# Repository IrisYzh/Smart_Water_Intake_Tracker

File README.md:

# Smart Water Intake Tracker

*The Smart Water Intake Tracker is a physical, non-intrusive system that helps users track their daily water intake through passive sensing and dynamic feedback.*  

This project consists of a smart sensing coaster and a desktop display device that together track and visualize a user’s daily water intake.

By passively detecting drinking events through weight changes and presenting progress via a mechanical gauge, the system encourages hydration without relying on screens or manual input.

---

## Sensor Device: Smart Coaster

### How it works
The sensing device is a smart coaster placed under a cup or bottle that detects drinking activity by monitoring weight changes. 

A load cell measures the applied force, and the signal is amplified, digitized, and processed by a microcontroller to estimate water intake based on relative weight differences over time.

### Key features
- **Drink Detection**: When the sensor detects that the cup has been lifted, the LED on the coaster begins to pulse, indicating that it's monitoring for weight changes.

- **Upload Status**: Once the weight change is detected and successfully uploaded to the display device, the coaster lights up green for 3 seconds. If the upload fails, it lights up red for 3 seconds instead.

- **Hydration Reminder**: If the system detects that the user hasn't had any water for 2 hours (no weight changes detected), the coaster will pulse to remind the user to stay hydrated.

### Key components
- **RGB LED**: [NeoPixel](Datasheets/SK6812RGBW-Neopixel.pdf)
- [**TAL221 Load Cell**](Datasheets/TAL221.pdf)  
- [**HX711 Load Cell Amplifier**](Datasheets/hx711_english.pdf)
- [**Seeed Studio XIAO ESP32-C3**](Datasheets/Seeed-Studio-XIAO-Series-SOM-Datasheet.pdf)
- **Communication**: Bluetooth Low Energy (BLE)

### Usage Modes
- **Sleep**: Device is off, minimal power consumption

- **Monitoring**: Continuously checks weight every 3 seconds with LED feedback

- **Detecting**: Actively detects weight changes and transmits data via BLE

---

## Display Device: Desktop Hydration Gauge

### How it works
The display device is a desktop hydration gauge that gives you a quick view of your daily water intake. It has a mechanical needle that shows your progress from 0–100%, an RGB LED ring for color-coded feedback, and a physical reset button to restart daily tracking.

### Key features
- **Visual Progress Tracking**: When the gauge receives a signal from the coaster, the needle moves to show how much water you've drunk today. The OLED screen below displays the exact amount and your progress percentage toward the daily goal.

- **Customizable Goals**: You can press the button below the dial to reset your data, or use the rotary knob to adjust your target water intake. All information shows up on the OLED screen.

### Key components
- **X27 Stepper Motor**
- **RGB LED**: [NeoPixel](Datasheets/SK6812RGBW-Neopixel.pdf)
- [**Seeed Studio XIAO ESP32-C3**](Datasheets/Seeed-Studio-XIAO-Series-SOM-Datasheet.pdf)
- [**SSD1306 OLED**](Datasheets/SSD1306.pdf) (Show the number)
- [**Rotary encoder**](Datasheets/RotaryEncoder-pec11.pdf) (Set/Change the goal)
- **Reset button**
- **Communication**: Bluetooth Low Energy (BLE)

### Usage Modes
- **Sleep**: Device is off, screen and motors powered down

- **Displaying**: Shows current hydration data with ambient lighting

- **Adjusting**: User interacts with buttons and rotary encoder to change settings

---

## Device-to-device communication

The smart coaster sends processed intake data to the display device wirelessly using Bluetooth Low Energy (BLE).  
Only high-level intake events (e.g., estimated water consumed) are transmitted, minimizing bandwidth and power usage.

### System workflow
1. The load cell detects weight changes when the user interacts with the cup  
2. The HX711 amplifies and digitizes the signal  
3. The microcontroller filters noise and detects valid drinking events  
4. Estimated intake values are accumulated locally  
5. Intake data is transmitted via BLE to the display device  
6. The display updates the mechanical needle and LED ring in real time  

This modular architecture separates sensing and feedback, making the system easier to debug, extend, and maintain.

## System Architecture

### Schematic

### PCB Design

---

## Datasheets

All component datasheets are included in the `/datasheets` folder of this repository.

- [TAL221 Load Cell Datasheet](Datasheets/TAL221.pdf)  
- [HX711 Load Cell Amplifier](Datasheets/hx711_english.pdf)  
- [Seeed Studio XIAO ESP32-C3](Datasheets/Seeed-Studio-XIAO-Series-SOM-Datasheet.pdf)  
- [OLED SSD1306](Datasheets/SSD1306.pdf)
- [Rotary Encoder](Datasheets/RotaryEncoder-pec11.pdf)
- [Neopixel](Datasheets/SK6812RGBW-Neopixel.pdf)

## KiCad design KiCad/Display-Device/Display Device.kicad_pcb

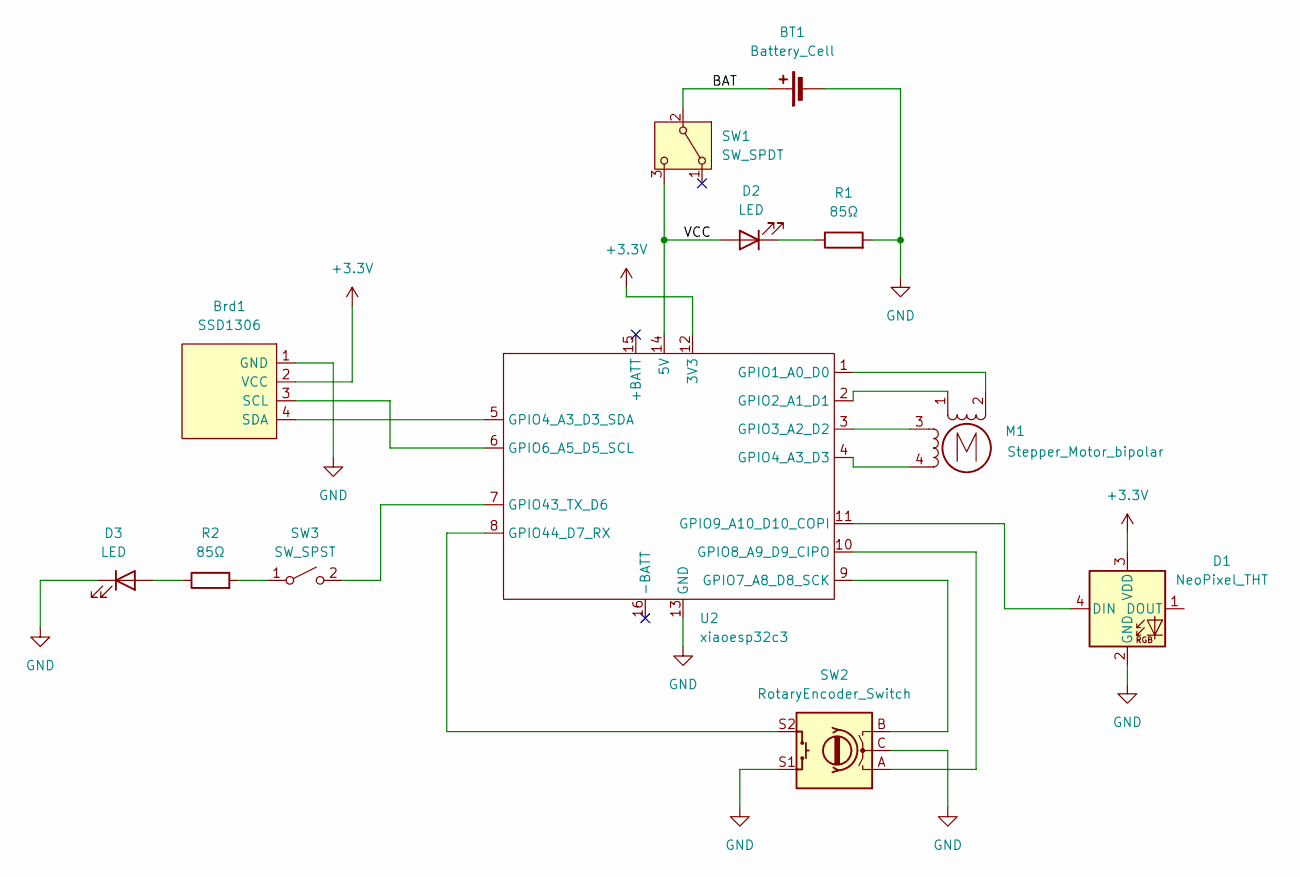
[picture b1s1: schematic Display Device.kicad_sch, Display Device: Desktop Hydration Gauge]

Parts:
BT1: Battery_Cell; PinSocket_1x02_P2.54mm_Vertical
Brd1: SSD1306; 128x64OLED
D1: NeoPixel_THT; PinSocket_1x04_P2.54mm_Vertical
D2, D3: LED; LED_0805_2012Metric_Pad1.15x1.40mm_HandSolder
M1: Stepper_Motor_bipolar; x27_stepper
R1, R2: 85Ω; R_0805_2012Metric_Pad1.20x1.40mm_HandSolder
SW1: SW_SPDT; PinSocket_1x03_P2.54mm_Vertical
SW2: RotaryEncoder_Switch; RotaryEncoder_Alps_EC11E-Switch_Vertical_H20mm
SW3: SW_SPST; PinSocket_1x02_P2.54mm_Vertical
U2: xiaoesp32c3; XIAO_ESP32

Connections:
+3.3V: Brd1.2 (VCC), D1.3 (VDD), U2.12 (3V3)
/BAT: BT1.1 (+), SW1.2 (B)
/VCC: D2.2 (A), SW1.3 (C), U2.14 (5V)
GND: BT1.2 (-), Brd1.1 (GND), D1.2 (GND), D3.1 (K), R1.2, SW2.C, SW2.S1, U2.13 (GND)
unnamed: Brd1.3 (SCL), U2.6 (GPIO6_A5_D5_SCL)
unnamed: Brd1.4 (SDA), U2.5 (GPIO4_A3_D3_SDA)
unnamed: D1.4 (DIN), U2.11 (GPIO9_A10_D10_COPI)
unnamed: D2.1 (K), R1.1
unnamed: D3.2 (A), R2.1
unnamed: M1.2 (-), U2.1 (GPIO1_A0_D0)
unnamed: R2.2, SW3.1 (A)
unnamed: SW3.2 (B), U2.7 (GPIO43_TX_D6)
unnamed: M1.1, U2.2 (GPIO2_A1_D1)
unnamed: M1.3, U2.3 (GPIO3_A2_D2)
unnamed: M1.4, U2.4 (GPIO4_A3_D3)
unnamed: SW2.B, U2.9 (GPIO7_A8_D8_SCK)
unnamed: SW2.A, U2.10 (GPIO8_A9_D9_CIPO)
unnamed: SW2.S2, U2.8 (GPIO44_D7_RX)

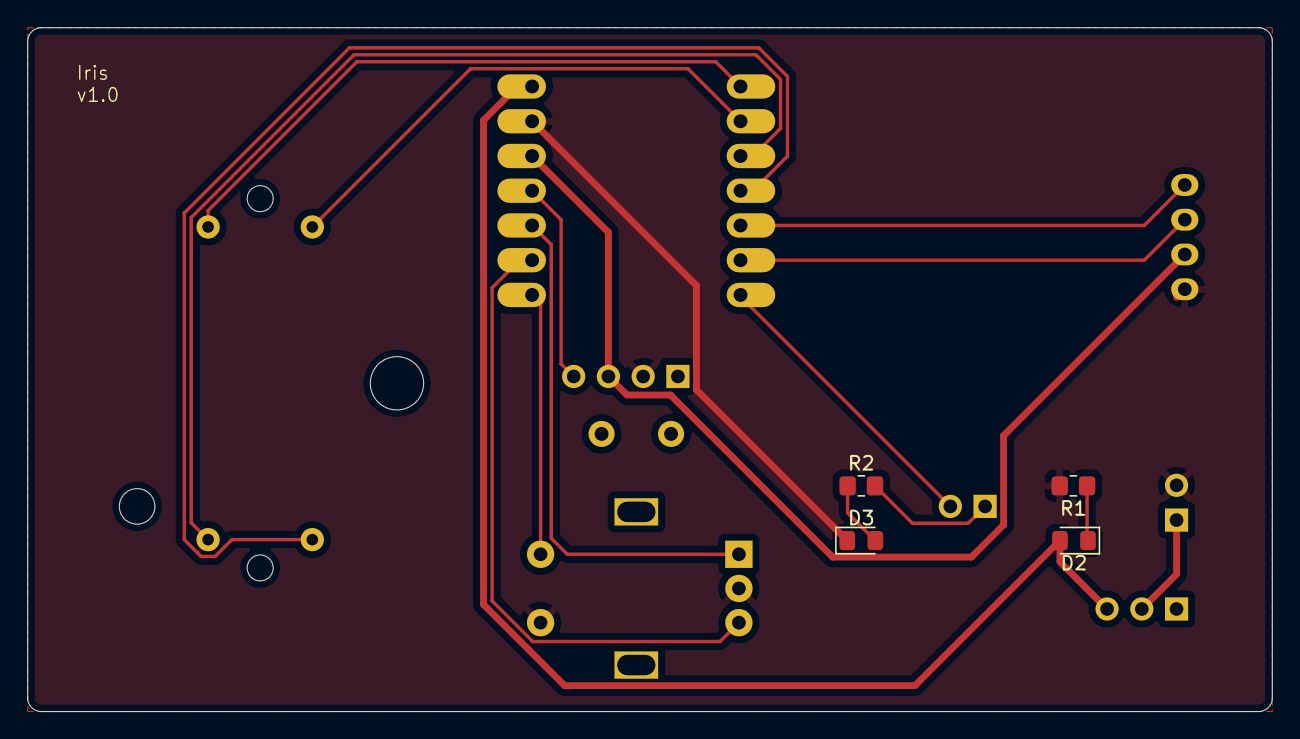
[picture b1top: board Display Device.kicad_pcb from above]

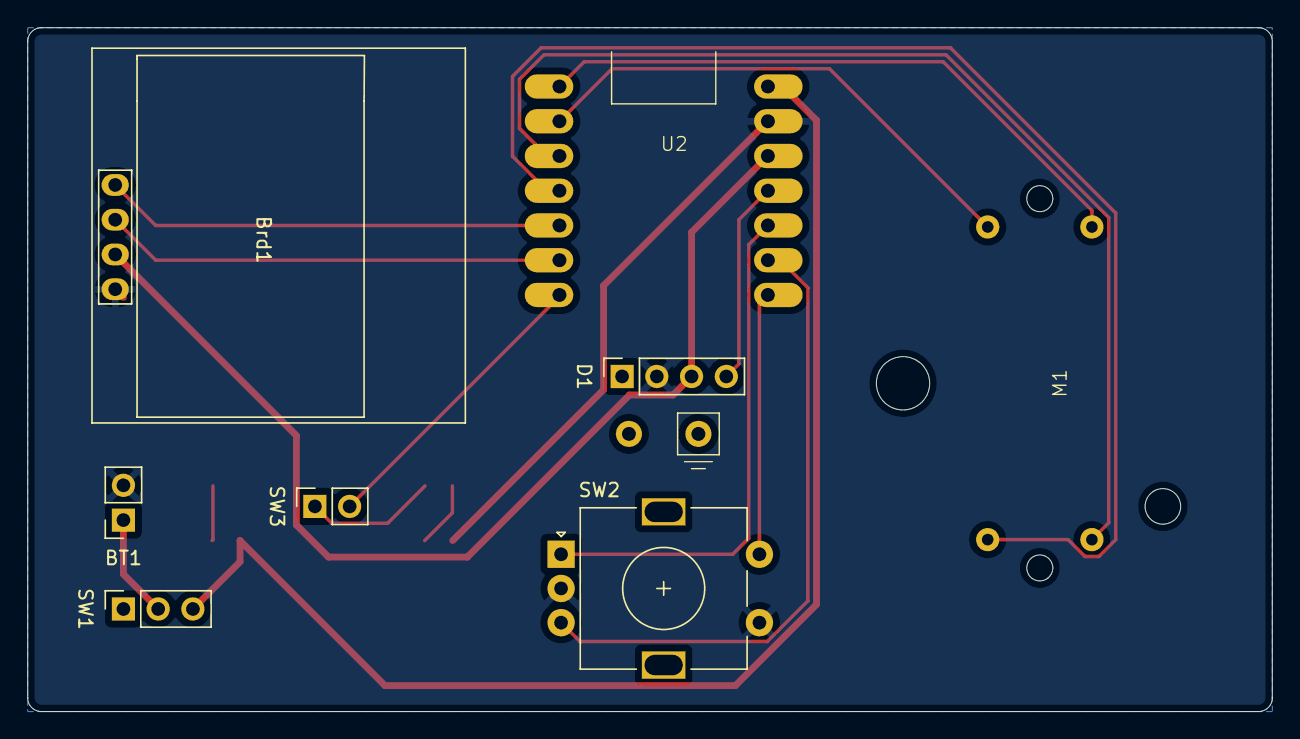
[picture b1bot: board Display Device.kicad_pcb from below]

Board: 2 copper layers, 91.0 x 50.0 mm, 12 parts (8 on the bottom side), 18 nets.

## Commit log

2026-01-27 Update Schematic Diagram
2026-01-27 update BOM
2026-02-03 update v2.0 pcb & schematic
2026-02-08 update datasheet
2026-02-08 update power model calculation
